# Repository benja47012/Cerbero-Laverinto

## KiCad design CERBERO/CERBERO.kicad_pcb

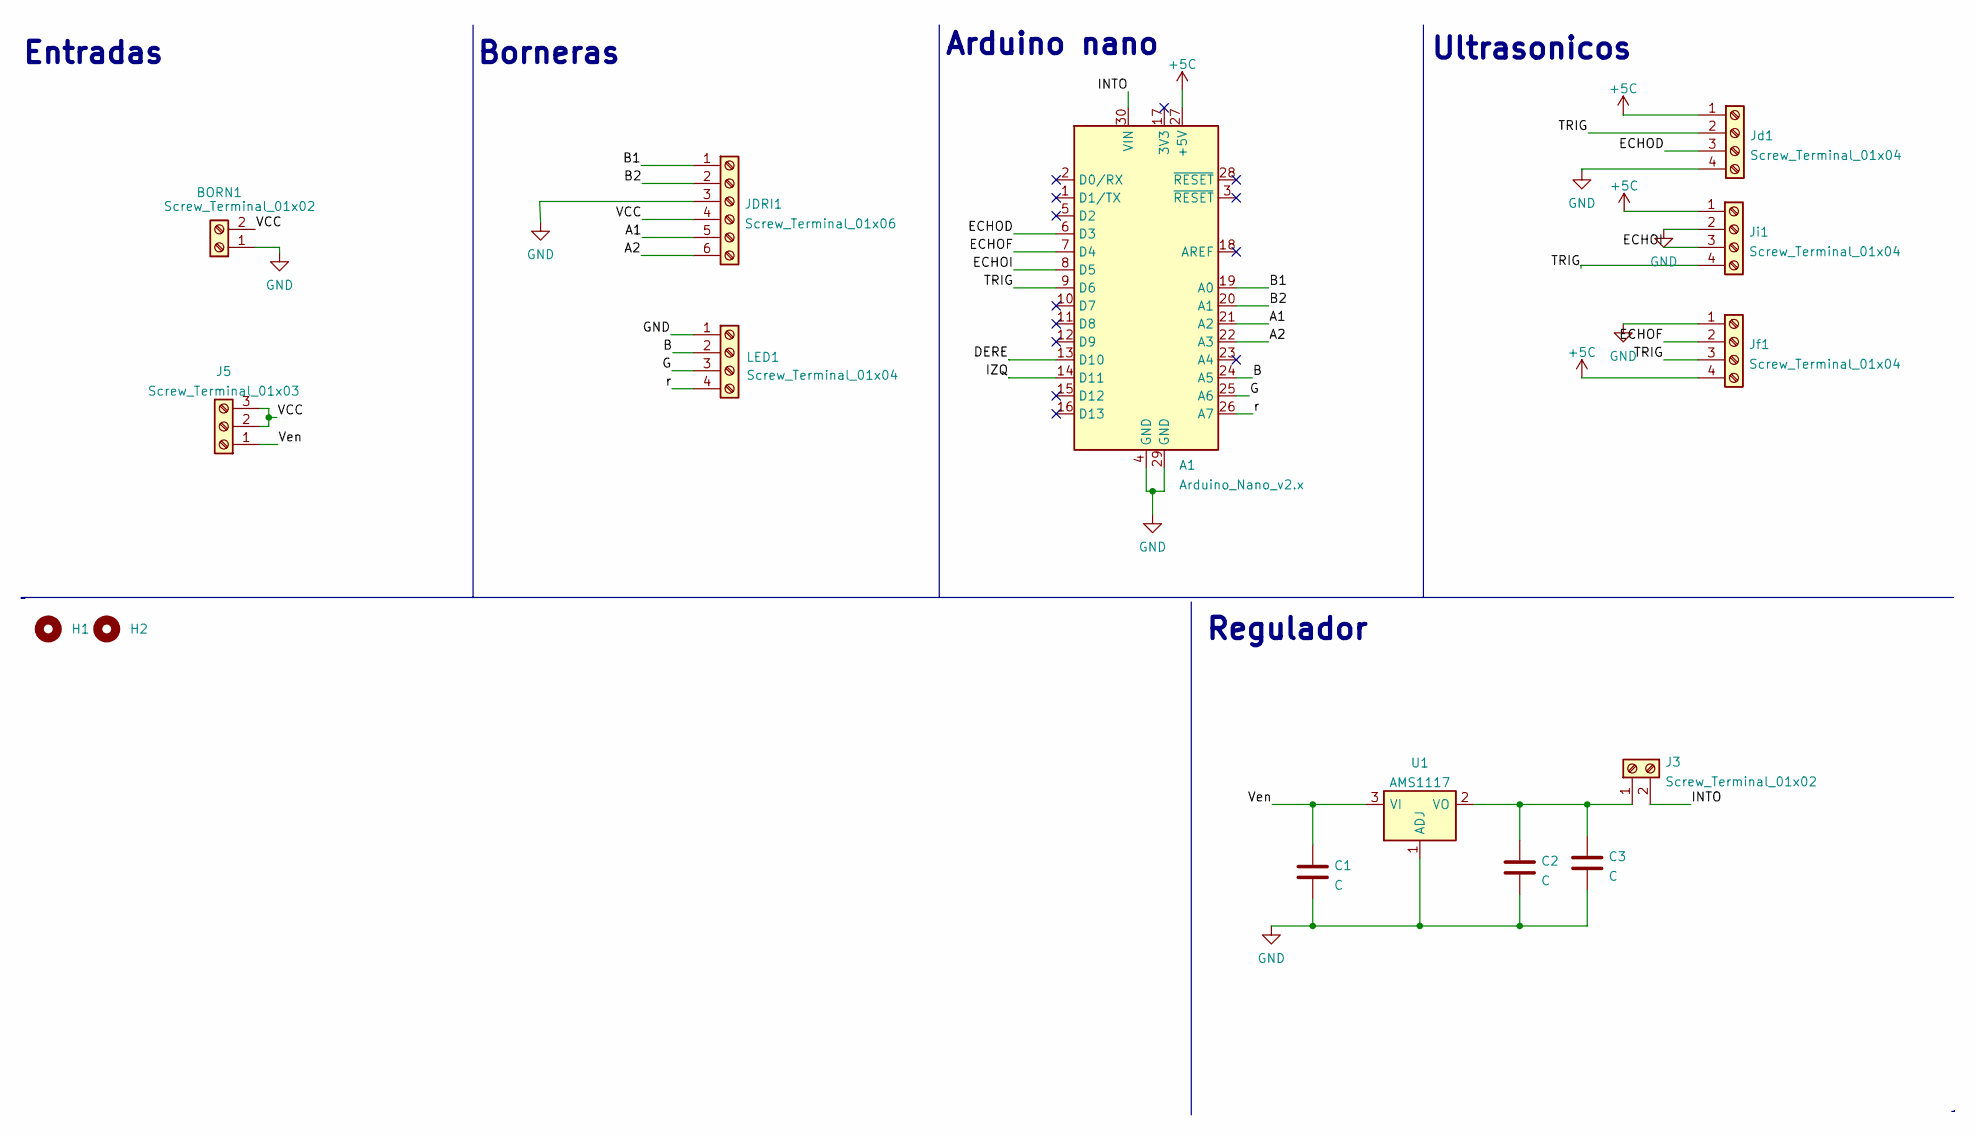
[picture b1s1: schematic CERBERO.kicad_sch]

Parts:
A1: Arduino_Nano_v2.x; Arduino_Nano
BORN1: Screw_Terminal_01x02; BORNERA2_AZUL
C1, C2, C3: C; CP_Radial_D6.3mm_P2.50mm
H1, H2: Mounting_Hole; Pololu_Micro_Con_Soporte_Simple
J3: Screw_Terminal_01x02; PinHeader_1x02_P2.54mm_Vertical
J5: Screw_Terminal_01x03; BORNERA3_AZUL
JDRI1: Screw_Terminal_01x06; PinHeader_1x06_P2.54mm_Vertical
Jd1: Screw_Terminal_01x04; JST_EH_B4B-EH-A_1x04_P2.50mm_Vertical
Jf1: Screw_Terminal_01x04; JST_EH_B4B-EH-A_1x04_P2.50mm_Vertical
Ji1: Screw_Terminal_01x04; JST_EH_B4B-EH-A_1x04_P2.50mm_Vertical
LED1: Screw_Terminal_01x04; PinHeader_1x04_P2.54mm_Vertical
U1: AMS1117; SOT-223-3_TabPin2

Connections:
+5C: A1.27 (+5V), Jd1.1, Jf1.4, Ji1.1
/A1: A1.21 (A2), JDRI1.5
/A2: A1.22 (A3), JDRI1.6
/B: A1.24 (A5), LED1.2
/B1: A1.19 (A0), JDRI1.1
/B2: A1.20 (A1), JDRI1.2
/DERE: A1.13 (D10)
/ECHOD: A1.6 (D3), Jd1.3
/ECHOF: A1.7 (D4), Jf1.2
/ECHOI: A1.8 (D5), Ji1.3
/G: A1.25 (A6), LED1.3
/INTO: A1.30 (VIN), J3.2
/IZQ: A1.14 (D11)
/TRIG: A1.9 (D6), Jd1.2, Jf1.3, Ji1.4
/VCC: BORN1.2, J5.2, J5.3, JDRI1.4
/Ven: C1.1, J5.1, U1.3 (VI)
/r: A1.26 (A7), LED1.4
GND: A1.4 (GND), A1.29 (GND), BORN1.1, C1.2, C2.2, C3.2, JDRI1.3, Jd1.4, Jf1.1, Ji1.2, LED1.1, U1.1 (ADJ)
unnamed: C2.1, C3.1, J3.1, U1.2 (VO)

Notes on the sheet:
Arduino nano
Regulador
Ultrasonicos
Borneras
Entradas

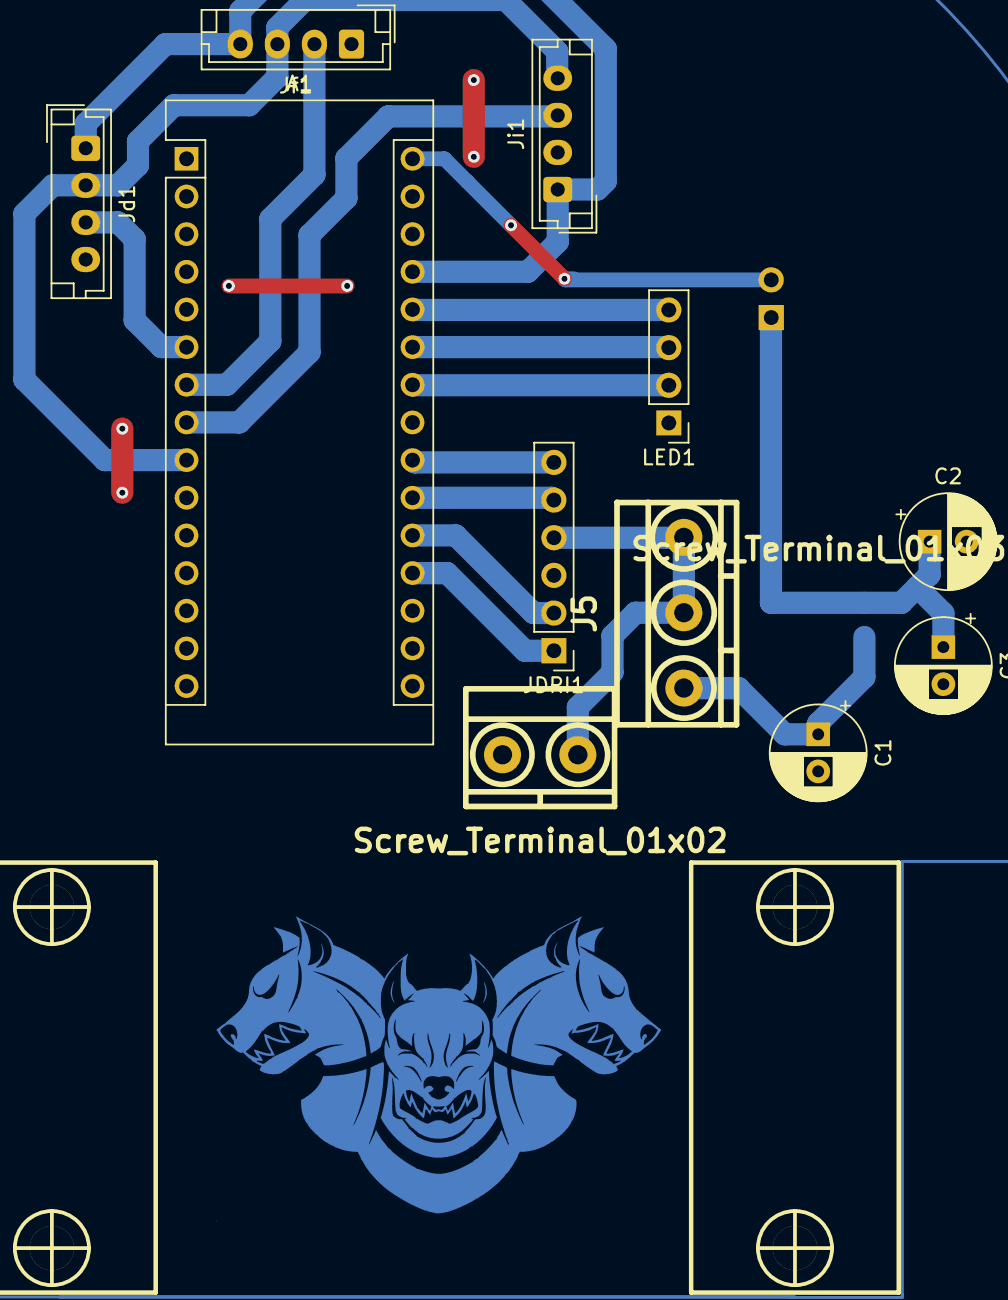
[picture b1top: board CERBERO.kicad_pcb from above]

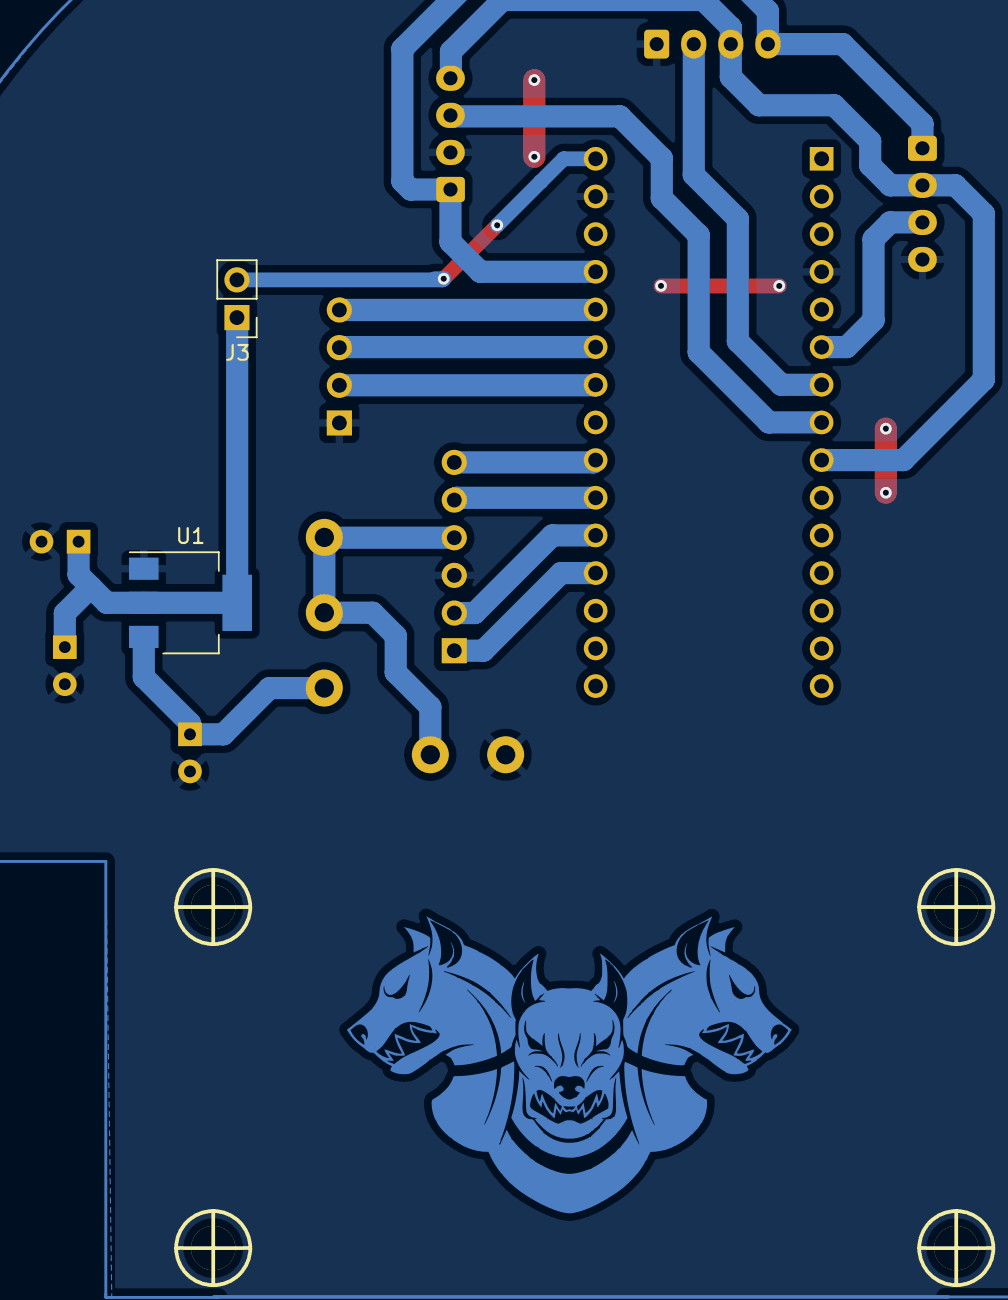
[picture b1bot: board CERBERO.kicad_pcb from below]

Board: 2 copper layers, 15 parts (2 on the bottom side), 17 nets.

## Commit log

2023-11-15 Cerbero-placa
